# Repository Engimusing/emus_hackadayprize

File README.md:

# emus_hackadayprize
DC LED Lighting

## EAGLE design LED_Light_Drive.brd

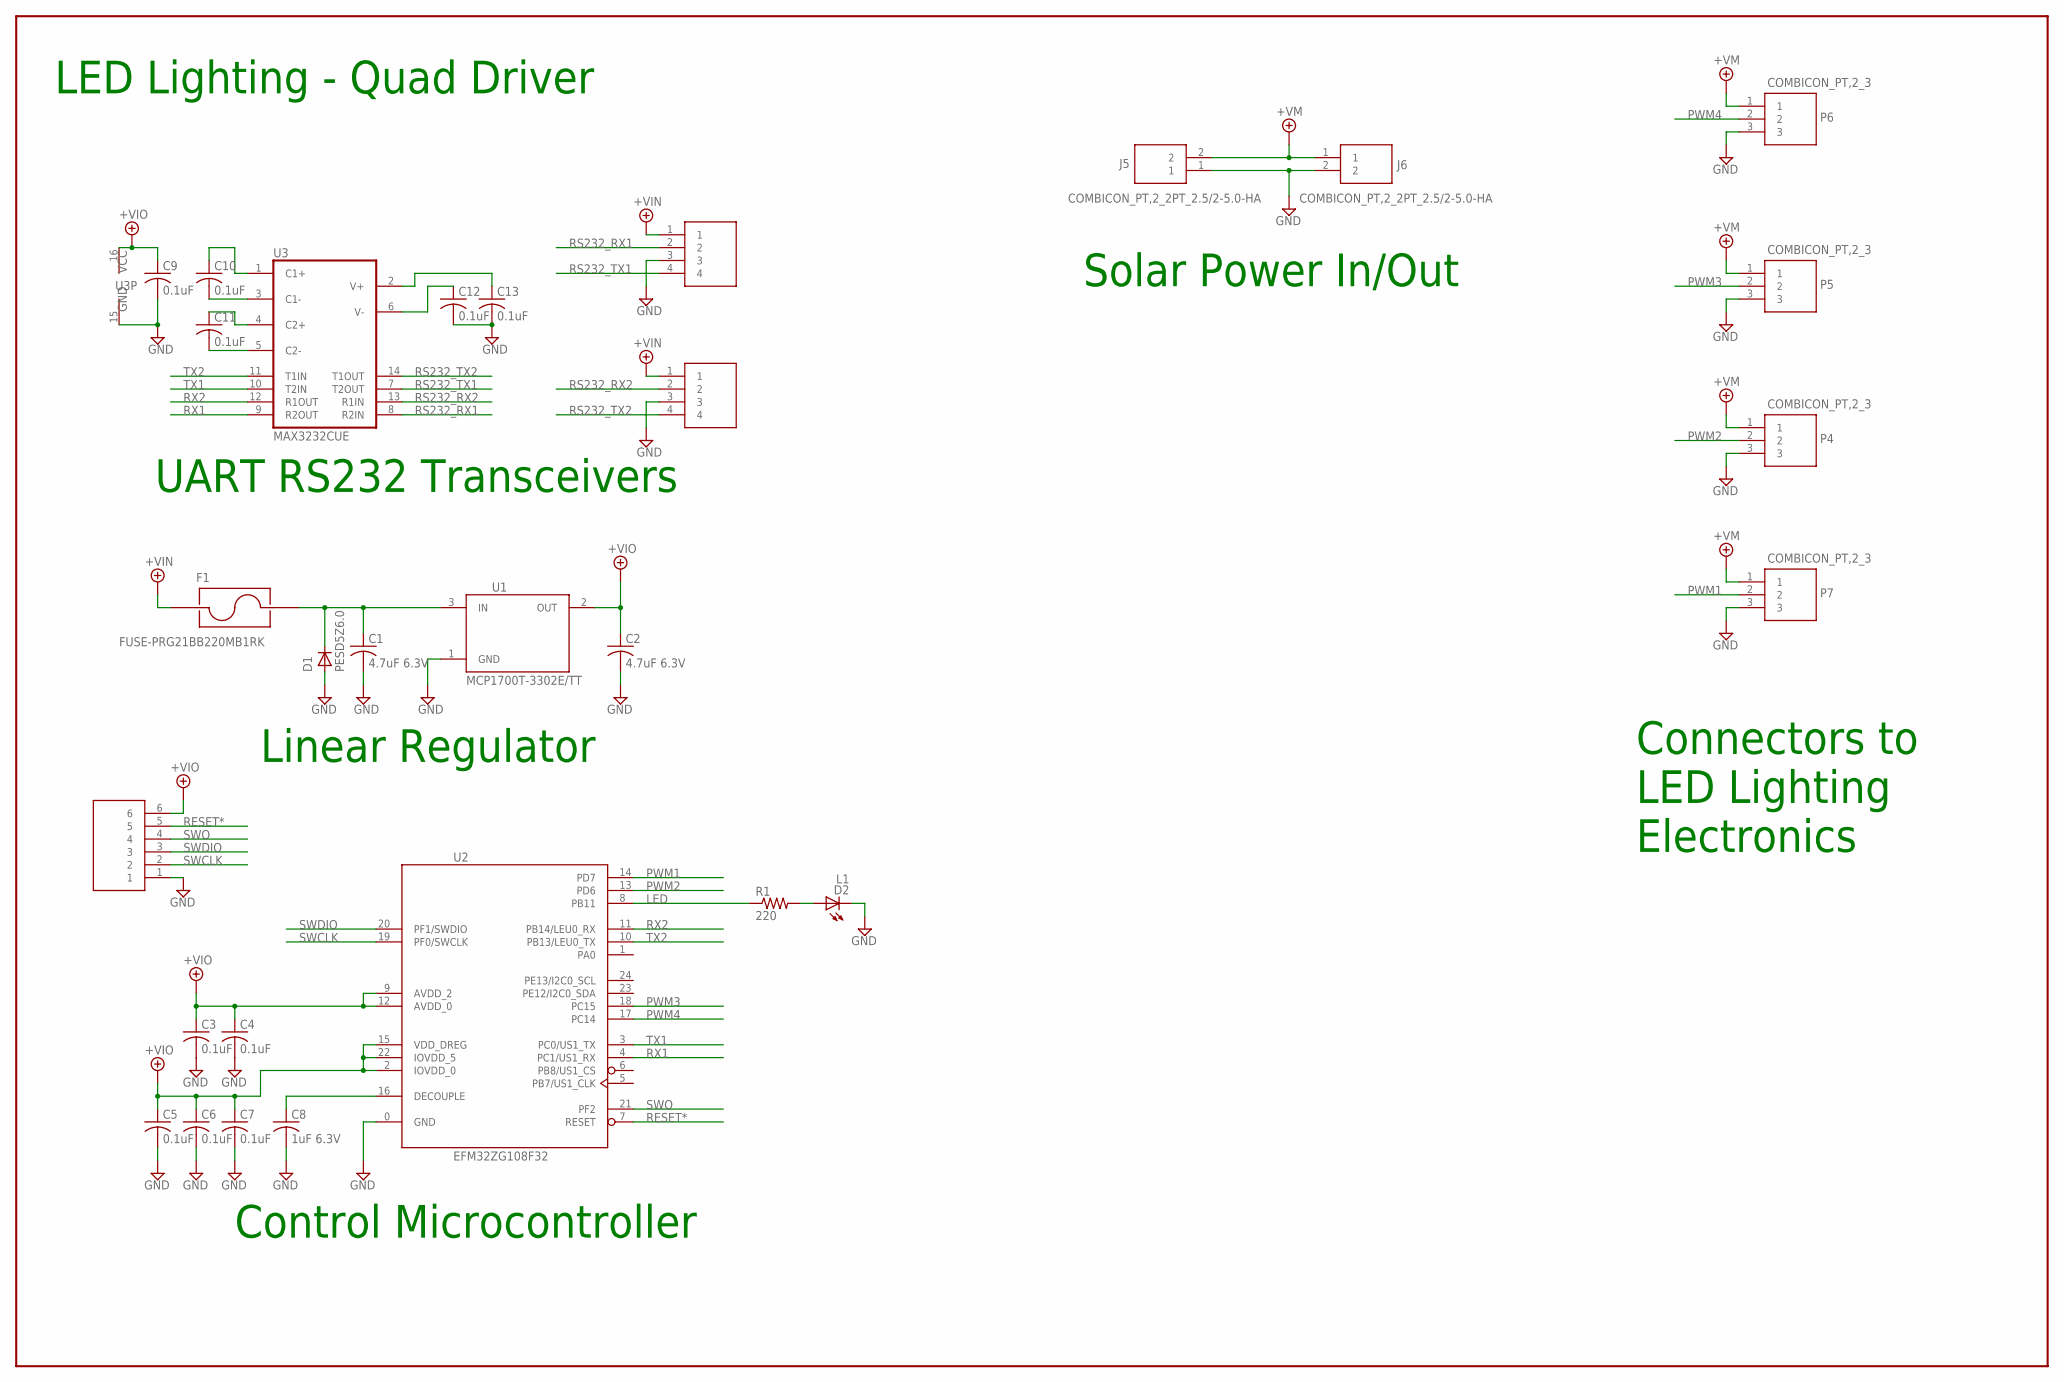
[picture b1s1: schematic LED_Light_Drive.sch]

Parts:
C1, C2: 4.7uF 6.3V; C0603
C3, C4, C5, C6, C7, C9, C10, C11, C12, C13: 0.1uF; C0402
C8: 1uF 6.3V; C0603
D1: PESD5Z6.0; SOD-523
D2: L1; CHIP-LED0603
F1: FUSE-PRG21BB220MB1RK; L0805_2.5
J5, J6: COMBICON_PT,2_2PT_2.5/2-5.0-HA; PT_2,5/2-5.0-HA
P1, P2: DF11-4_STRAIGHT_PIN; DF11SP-4-H
P3: DF11-6_STRAIGHT_PIN; DF11SP-6-H
P4, P5, P6, P7: COMBICON_PT,2_3; PT_2,5/3-5,0-H
R1: 220; R0402
U1: MCP1700T-3302E/TT; SOT23A
U2: EFM32ZG108F32; QFN24_5X5
U3: MAX3232CUE; TSSOP16

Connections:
+VIN: F1.2 (A), P1.1, P2.1
+VIO: C2.1, C3.1, C4.1, C5.1, C6.1, C7.1, C9.1, P3.6, U1.2 (OUT), U2.2 (IOVDD_0), U2.9 (AVDD_2), U2.12 (AVDD_0), U2.15 (VDD_DREG), U2.22 (IOVDD_5), U3.16 (VCC)
+VM: J5.2, J6.1, P4.1, P5.1, P6.1, P7.1
GND: C1.2, C2.2, C3.2, C4.2, C5.2, C6.2, C7.2, C8.2, C9.2, C12.2, C13.2, D1.A, D2.C, J5.1, J6.2, P1.3, P2.3, P3.1, P4.3, P5.3, P6.3, P7.3, U1.1 (GND), U2.0 (GND), U3.15 (GND)
LED: R1.1, U2.8 (PB11)
unnamed: C8.1, U2.16 (DECOUPLE)
unnamed: D2.A, R1.2
unnamed: C10.2, U3.3 (C1-)
unnamed: C10.1, U3.1 (C1+)
unnamed: C11.2, U3.5 (C2-)
unnamed: C11.1, U3.4 (C2+)
unnamed: C13.1, U3.2 (V+)
unnamed: C12.1, U3.6 (V-)
PWM1: P7.2, U2.14 (PD7)
PWM2: P4.2, U2.13 (PD6)
PWM3: P5.2, U2.18 (PC15)
PWM4: P6.2, U2.17 (PC14)
RESET*: P3.5, U2.7 (RESET)
RS232_RX1: P2.2, U3.8 (R2IN)
RS232_RX2: P1.2, U3.13 (R1IN)
RS232_TX1: P2.4, U3.7 (T2OUT)
RS232_TX2: P1.4, U3.14 (T1OUT)
RX1: U2.4 (PC1/US1_RX), U3.9 (R2OUT)
RX2: U2.11 (PB14/LEU0_RX), U3.12 (R1OUT)
SWCLK: P3.2, U2.19 (PF0/SWCLK)
SWDIO: P3.3, U2.20 (PF1/SWDIO)
SWO: P3.4, U2.21 (PF2)
TX1: U2.3 (PC0/US1_TX), U3.10 (T2IN)
TX2: U2.10 (PB13/LEU0_TX), U3.11 (T1IN)
VIN: C1.1, D1.K (C), F1.1 (B), U1.3 (IN)

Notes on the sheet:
UART RS232 Transceivers
LED Lighting - Quad Driver
Connectors to LED Lighting Electronics
Solar Power In/Out
Control Microcontroller
Linear Regulator

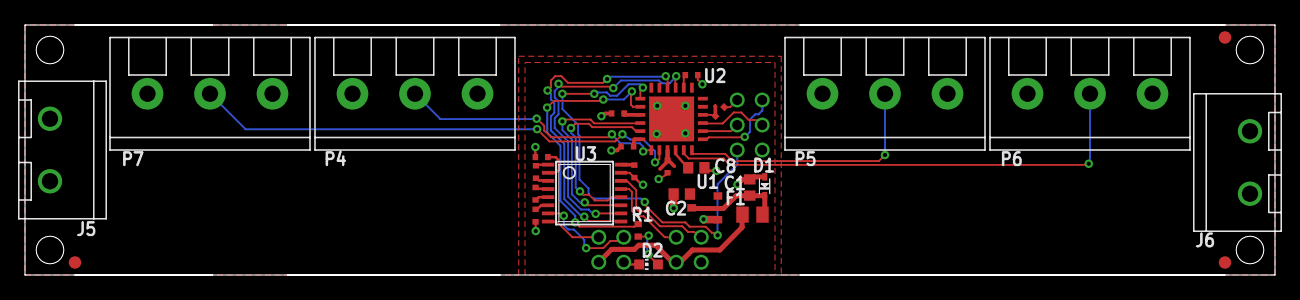
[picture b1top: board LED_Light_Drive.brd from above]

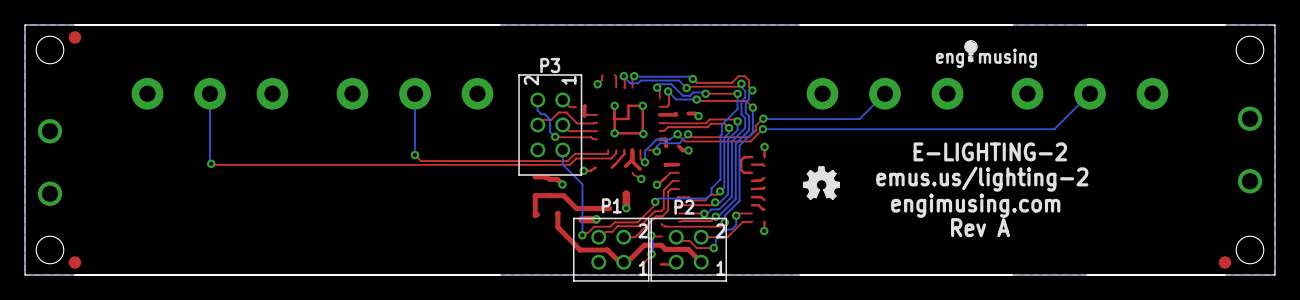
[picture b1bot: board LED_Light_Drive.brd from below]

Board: 2 copper layers, 100.0 x 20.0 mm, 34 parts (5 on the bottom side), 30 nets.

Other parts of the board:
U$1, U$2, U$5: FIDUCIAL_G10
U$3: OSHW_FILLX100_NOTEXT
U$4: LOGO

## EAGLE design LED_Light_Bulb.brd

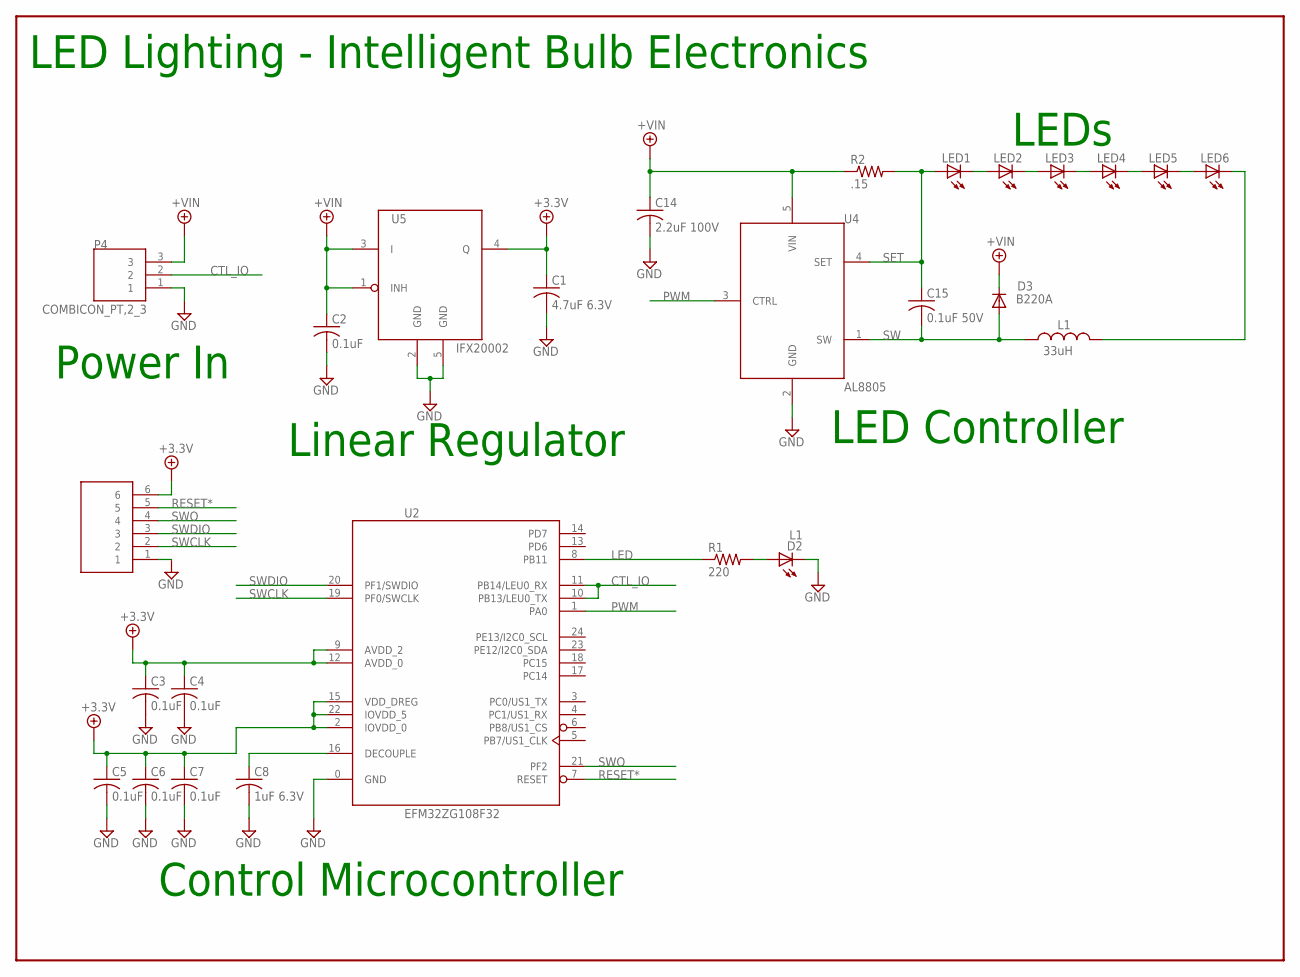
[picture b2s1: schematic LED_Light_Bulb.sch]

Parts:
C1: 4.7uF 6.3V; C0603
C2, C3, C4, C5, C6, C7: 0.1uF; C0603
C8: 1uF 6.3V; C0603
C14: 2.2uF 100V; C1210K
C15: 0.1uF 50V; C0805
D2: L1; CHIP-LED0603
D3: B220A; DO214SMA
L1: 33uH; SRN6045
LED1, LED2, LED3, LED4, LED5, LED6: LED-MX3; LED_5X5
P3: DF11-6_STRAIGHT_PIN; DF11SP-6-H
P4: COMBICON_PT,2_3; PT_2,5/3-5,0-H
R1: 220; R0603
R2: .15; R0805
U2: EFM32ZG108F32; QFN24_5X5
U4: AL8805; SOT-23-5A
U5: IFX20002; PG-SCT595-5

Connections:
+3.3V: C1.1, C3.1, C4.1, C5.1, C6.1, C7.1, P3.6, U2.2 (IOVDD_0), U2.9 (AVDD_2), U2.12 (AVDD_0), U2.15 (VDD_DREG), U2.22 (IOVDD_5), U5.4 (Q)
+VIN: C2.1, C14.1, D3.1 (C), P4.3, R2.1, U4.5 (VIN), U5.1 (INH), U5.3 (I)
CTL_IO: P4.2, U2.10 (PB13/LEU0_TX), U2.11 (PB14/LEU0_RX)
GND: C1.2, C2.2, C3.2, C4.2, C5.2, C6.2, C7.2, C8.2, C14.2, D2.C, P3.1, P4.1, U2.0 (GND), U4.2 (GND), U5.2 (GND), U5.5 (GND)
LED: R1.1, U2.8 (PB11)
unnamed: C8.1, U2.16 (DECOUPLE)
unnamed: L1.2, LED6.C
unnamed: D2.A, R1.2
unnamed: LED1.C, LED2.A
unnamed: LED2.C, LED3.A
unnamed: LED3.C, LED4.A
unnamed: LED4.C, LED5.A
unnamed: LED5.C, LED6.A
PWM: U2.1 (PA0), U4.3 (CTRL)
RESET*: P3.5, U2.7 (RESET)
SET: C15.1, LED1.A, R2.2, U4.4 (SET)
SW: C15.2, D3.2 (A), L1.1, U4.1 (SW)
SWCLK: P3.2, U2.19 (PF0/SWCLK)
SWDIO: P3.3, U2.20 (PF1/SWDIO)
SWO: P3.4, U2.21 (PF2)

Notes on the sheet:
LED Lighting - Intelligent Bulb Electronics
Power In
Linear Regulator
Control Microcontroller
LED Controller
LEDs

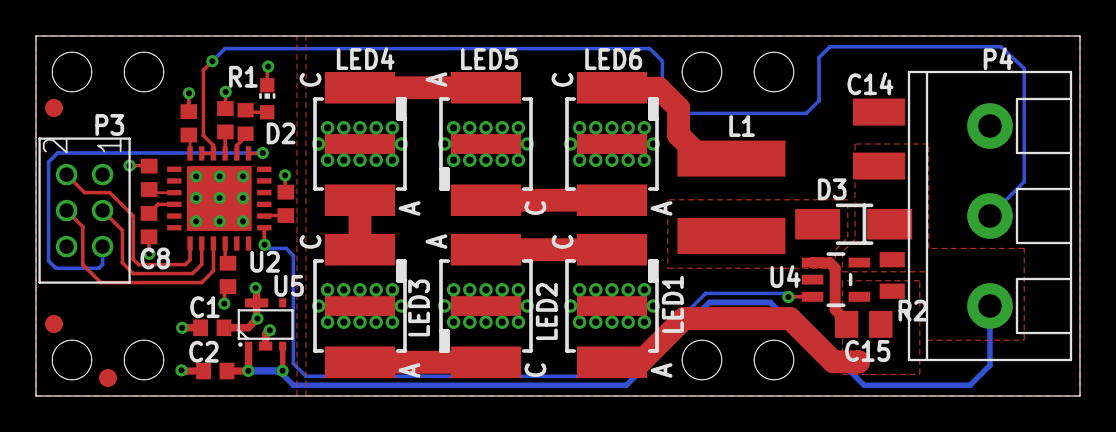
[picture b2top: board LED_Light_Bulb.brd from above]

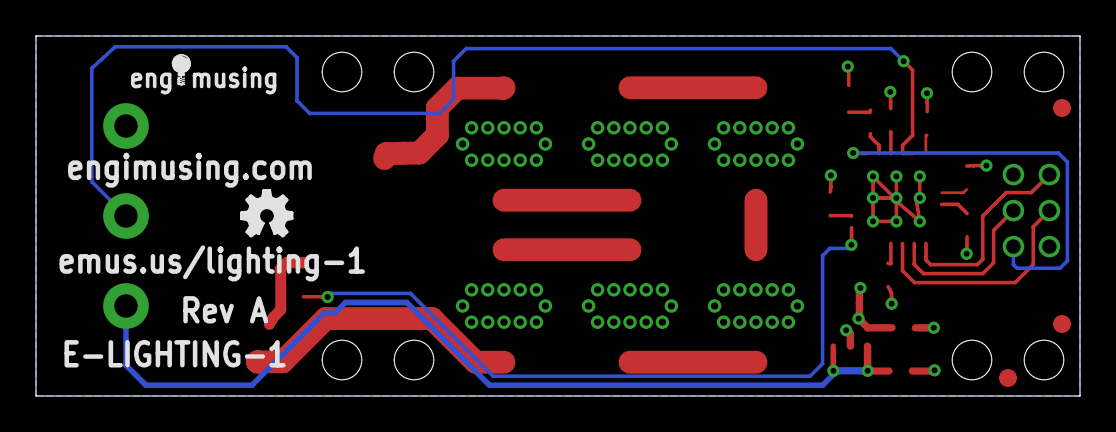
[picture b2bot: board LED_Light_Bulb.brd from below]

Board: 2 copper layers, 58.0 x 20.0 mm, 31 parts (2 on the bottom side), 20 nets.

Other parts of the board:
U$1, U$2, U$5: FIDUCIAL_G10
U$3: OSHW_FILLX100_NOTEXT
U$4: LOGO

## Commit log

2015-08-15 Added schematic and board files
2015-08-17 added design document

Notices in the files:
parts and their libraries:
dicons: Copyright (C) 2004, Bob Starr (rtzaudio@mindspring.com)
Engimusing: Released under the Creative Commons
Attribution Share-Alike 4.0 License
https://creativecommons.org/licenses/by-sa/4.0
